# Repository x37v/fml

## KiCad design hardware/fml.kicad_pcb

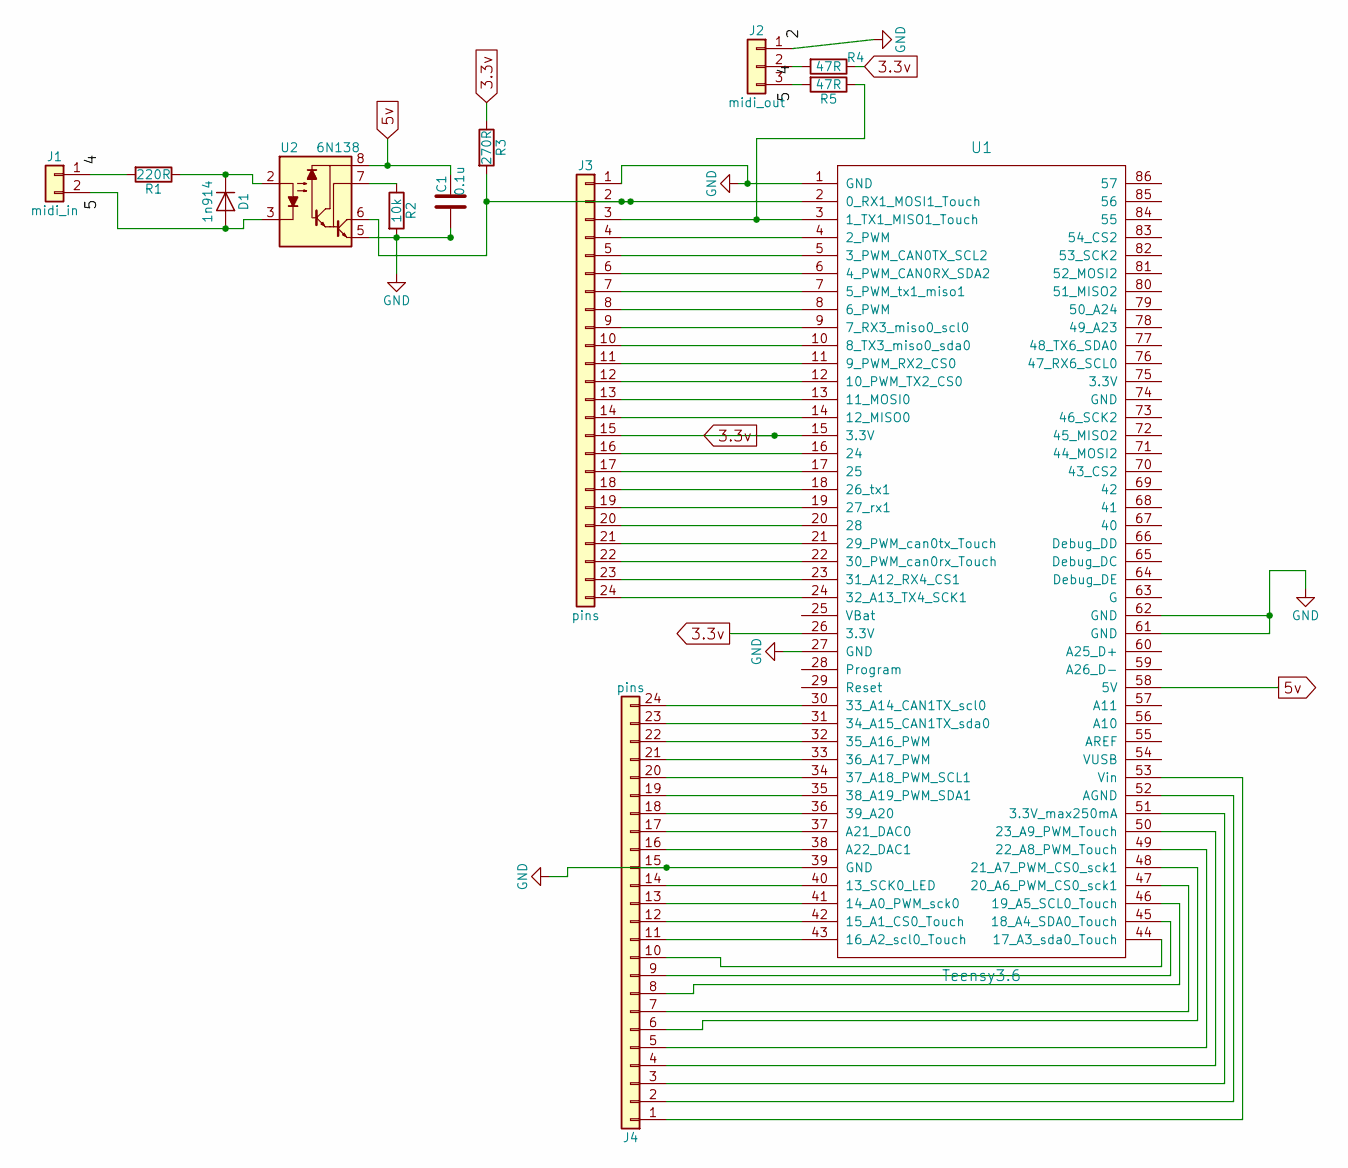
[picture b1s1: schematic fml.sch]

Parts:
C1: 0.1u; C_Disc_D5.0mm_W2.5mm_P2.50mm
D1: 1n914; D_A-405_P7.62mm_Horizontal
J1: midi_in; Pin_Header_Straight_1x02_Pitch2.54mm
J2: midi_out; Pin_Header_Straight_1x03_Pitch2.54mm
J3, J4: pins; Pin_Header_Straight_1x24_Pitch2.54mm
R1: 220R; Resistor_Horizontal_RM10mm-xnorman
R2: 10k; Resistor_Horizontal_RM10mm-xnorman
R3: 270R; Resistor_Horizontal_RM10mm-xnorman
R4, R5: 47R; Resistor_Horizontal_RM10mm-xnorman
U1: Teensy3.6; Teensy35_36
U2: 6N138; DIP-8_W7.62mm

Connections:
3.3v: J3.15, R3.1, R4.1, U1.15 (3.3V), U1.26 (3.3V)
5v: C1.2, U1.58 (5V), U2.8
GND: C1.1, J2.1, J3.1, J4.15, R2.2, U1.1 (GND), U1.27 (GND), U1.39 (GND), U1.61 (GND), U1.62 (GND), U2.5
unnamed: D1.1 (K), R1.1, U2.2
unnamed: D1.2 (A), J1.2, U2.3
unnamed: J1.1, R1.2
unnamed: J2.2, R4.2
unnamed: J2.3, R5.2
unnamed: J3.2, R3.2, U1.2 (0_RX1_MOSI1_Touch), U2.6
unnamed: J3.3, R5.1, U1.3 (1_TX1_MISO1_Touch)
unnamed: J3.4, U1.4 (2_PWM)
unnamed: J3.5, U1.5 (3_PWM_CAN0TX_SCL2)
unnamed: J3.6, U1.6 (4_PWM_CAN0RX_SDA2)
unnamed: J3.7, U1.7 (5_PWM_tx1_miso1)
unnamed: J3.8, U1.8 (6_PWM)
unnamed: J3.9, U1.9 (7_RX3_miso0_scl0)
unnamed: J3.10, U1.10 (8_TX3_miso0_sda0)
unnamed: J3.11, U1.11 (9_PWM_RX2_CS0)
unnamed: J3.12, U1.12 (10_PWM_TX2_CS0)
unnamed: J3.13, U1.13 (11_MOSI0)
unnamed: J3.14, U1.14 (12_MISO0)
unnamed: J3.16, U1.16 (24)
unnamed: J3.17, U1.17 (25)
unnamed: J3.18, U1.18 (26_tx1)
unnamed: J3.19, U1.19 (27_rx1)
unnamed: J3.20, U1.20 (28)
unnamed: J3.21, U1.21 (29_PWM_can0tx_Touch)
unnamed: J3.22, U1.22 (30_PWM_can0rx_Touch)
unnamed: J3.23, U1.23 (31_A12_RX4_CS1)
unnamed: J3.24, U1.24 (32_A13_TX4_SCK1)
unnamed: J4.1, U1.53 (Vin)
unnamed: J4.2, U1.52 (AGND)
unnamed: J4.3, U1.51 (3.3V_max250mA)
unnamed: J4.4, U1.50 (23_A9_PWM_Touch)
unnamed: J4.5, U1.49 (22_A8_PWM_Touch)
unnamed: J4.6, U1.48 (21_A7_PWM_CS0_sck1)
unnamed: J4.7, U1.47 (20_A6_PWM_CS0_sck1)
unnamed: J4.8, U1.46 (19_A5_SCL0_Touch)
unnamed: J4.9, U1.45 (18_A4_SDA0_Touch)
unnamed: J4.10, U1.44 (17_A3_sda0_Touch)
unnamed: J4.11, U1.43 (16_A2_scl0_Touch)
unnamed: J4.12, U1.42 (15_A1_CS0_Touch)
unnamed: J4.13, U1.41 (14_A0_PWM_sck0)
unnamed: J4.14, U1.40 (13_SCK0_LED)
unnamed: J4.16, U1.38 (A22_DAC1)
unnamed: J4.17, U1.37 (A21_DAC0)
unnamed: J4.18, U1.36 (39_A20)
unnamed: J4.19, U1.35 (38_A19_PWM_SDA1)
unnamed: J4.20, U1.34 (37_A18_PWM_SCL1)
unnamed: J4.21, U1.33 (36_A17_PWM)
unnamed: J4.22, U1.32 (35_A16_PWM)
unnamed: J4.23, U1.31 (34_A15_CAN1TX_sda0)
unnamed: J4.24, U1.30 (33_A14_CAN1TX_scl0)
unnamed: R2.1, U2.7

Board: 2 copper layers, 13 parts (0 on the bottom side), 54 nets, no tracks yet.

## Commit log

2015-06-20 initial setup
2015-06-20 initial setup that does nothing yet
2015-06-20 making some sound, very basic
2015-06-20 envelopes and basic synth container
2015-06-20 calculating and using dependencies in makefile
2015-06-20 setting frequency
2015-06-21 very simple note input
2015-06-21 note allocation with complete callbacks.. have some stuck note problem though
2015-06-21 no longer triggering off on reclaim voice
2015-06-21 make sure that we have non zero stage settings
2015-06-21 found stuck note problem
    the same note can be triggered multiple times. do we want this?
2015-06-21 think I've dealt with, for now.. the ramp up click sound
2015-06-21 starting to hook in CC controls
2015-06-21 mapping some CCs to envelopes
2015-06-21 toned back the feedback
2015-07-11 AD and AR envelope
2015-08-26 added description text to git project
2015-08-26 added notes for clarification
2015-09-03 updates from greg/andre meet
2015-09-03 both envelope types have callback settings now, fixed up name
2015-09-03 switched envelope types, remapping velocity
2015-09-03 passing along velocity and working with new envelope types
2015-09-03 trying to deal with immediate envelopes but they don't seem to be working quite right yet
2015-09-03 moved scaling into synth..
    depth and feedback scaling
2015-09-03 made feedback scaling a little more readable
2015-09-04 a bunch of tweaks
2015-09-04 brought velocity back in
2015-10-18 added exponential ADSR, rudimentary right now
2015-10-18 mapped in control of envelope params
2015-10-18 setting release for volume not decay, min is 15ms
2015-10-23 for testing, separated cc and note channel
    cuz quneo is sending CCs with notes..
2015-10-23 make task to run and hook up midi
2015-10-23 starting on mono mode, getting some clicking..
2015-10-24 wait a second until we try to hook to jack
2015-10-24 ignore velocity when retriggering..
    gets rid of clicks, is this how we want to work??
2015-10-25 really basic slew in place
2015-10-25 always slewing a little, getting closer
2015-10-25 defaulting to very little slew
2015-10-25 mod depth interpolation
2015-10-28 slewing velocity
2015-10-28 when a note is down in mono mode, only set freq.. don't even play with env
2015-10-29 allow for zero length attack and decay
2015-10-29 don't auto connect to audio
2015-10-29 run connected to output 3
2015-10-29 changed default settings for mod envelope
2015-10-30 working on fixed modes, frequency isn't quite right yet though
2015-10-30 fixed modes seem to work
2015-11-08 CCs now change mode in the extremes of the ratio settings
2015-11-08 connect to a bunch more midi if you can
2015-11-08 swapped fixed carrier and fixed modulator
2015-11-27 global volume control hooked up
2015-11-27 printing out more info from midiproc
2015-11-27 increased volume env's sustain to 10 seconds
2015-11-28 feedback and mod offset instantaneous phase but don't accumulate
    I think this fixes both the feedback and fine tuning issues
2015-11-28 ditched initial conditions in main for synth
2015-11-28 feedback now goes to 1
2015-11-28 smoothing modulator fine tune, always updating increments before computing
2015-11-28 linearly smoothing function, using in a bunch of places
2015-11-28 lin smooth mod depth as well
2015-11-28 much better slew, slewing freq with a linear ramp
2015-11-28 ditched mono mode
2015-11-28 slew is squared.. not sure if thats ideal but thats in the prototype
2015-12-02 removed exp slew, added more ratio steps
2015-12-02 if slew increment is zero, just jump
2015-12-02 increased the max slew increment
2015-12-09 slew is getting a little more reasonable, can turn it off now
2015-12-09 using the enumeration for env state
2015-12-09 envelope state getters
2015-12-09 new voice allocation scheme..
    same note, free note, releasing note, LRU
2015-12-10 more ratios!
2015-12-10 linearly smooth offset value, updated range in fixed mode
2015-12-10 using midi for fixed mode freq is much nicer, exponential
2015-12-15 allow for negative increments with lin_smooth
2015-12-15 using midi notes internally and slewing those, based seconds per octave
2015-12-21 only set slew note when we're idle
    this way slew will start where the synth was if its not idle
2015-12-21 removed printouts in midi proc
2015-12-21 more reasonable mod env initial settings
2015-12-21 better mod env settings, clicks gone??
2015-12-21 mod depth no longer zippery
2015-12-21 increments are stored in member variable so we know which direction we're going
    no more zipper noise?
2015-12-21 moved note and slew settings to their own method
    so we can use for mono mode
2015-12-21 mono mode midi setting, kill all notes when we switch
2015-12-21 mono mode always slews at slew rate from last note
2015-12-21 mono mode is now CC 58
2015-12-22 pitch bend!
2015-12-22 have basic transpose
2015-12-22 increased global volume
2015-12-22 stereo preparation
2015-12-22 stereo detune mode first go
2015-12-22 decreased detune
2015-12-22 fixed clicking on velocity
2015-12-22 poly mode, slewing from first held note
2015-12-22 always set slew note
2015-12-22 last of the linear smooth increment sign fixes [i think]
2015-12-22 oops, ?
2015-12-22 extended the envelopes
2015-12-22 don't turn off notes on change to mono mode
2015-12-23 using the envelope state to figure out slewing
    poly mode always slews, but if notes are held it slews from the first
    held note
    mono mode only slews when a note is held, and always slews from the last
    note hit
2015-12-23 transpose is in octave increments only
2015-12-23 moved voice allocation into 'synth'
2015-12-23 midi setting for making mod envelope linear
2015-12-23 keeping track of notes down.. to be used in mono mode
2016-01-19 smoothing feedback amount
    removed zipper noise
2016-01-19 added stm32f4xx-gcc-barebones project to start from
2016-01-19 moved barebones project
2016-01-19 renamed arm project
2016-01-19 ignoring library files and build directories
2016-01-19 updated gdb init with new project name
2016-01-19 made targets for starting openocd and gdb
2016-01-19 renamed the debug target to gdb
2016-01-21 leds work now!
2016-01-21 quick and dirty, leds now reflect button state
2016-01-21 using C++ now
2016-02-29 think i now have the dac 1/2 and full interrupts working
2016-03-03 flailing, still not hitting the interrupts i want
    I'm seeing TEIF6 and DMEIF6
2016-03-03 removed extra semicolon
2016-03-29 getting the full and half transfer callbacks..
    oops, was testing the wrong bit!!
2016-03-29 making a tone in the dma transfer.. need to work on output freq etc
2016-04-05 using the auto reload register
2016-04-05 playing with sine freq
    can't tell if its just the output not being filtered or what, it ain't
    right yet
2016-04-25 have approximately 44.1khz SR with sine wave
2016-04-25 have a chirp sound going now
2016-04-25 clean up
2016-04-25 pin layout
2016-04-25 have dual mode going but can't seem to compute sine for both without underruns
2016-04-25 computing sine just fine with arm_sin_f32
2016-04-26 reorg
2016-04-26 updated makefile and ignores
2016-04-26 fixed up clean for jack
2016-04-26 move lib to top dir and added notes about how to get it
    not including it in project because i'm not sure about the license
2016-04-26 cleaning up directories
2016-04-26 got buttons back in, increased buffer size
2016-04-28 fixed conversion from float to int12, no more clicks!
2016-04-28 oops, forgot to cleanup main
2016-04-29 making build directory if needed
2016-04-29 some of the fm code is building, need to add callbacks back
2016-04-30 added arm gcc version to readme
2016-04-30 updated readme and makefile
2016-04-30 updated readme with markdown formatting
2016-04-30 more formatting
2016-04-30 even more formatting
2016-04-30 more markdown
2016-04-30 super crippled but making sound on jack
2016-04-30 doesn't sound at all like what it should but arm chip is making sound
2016-05-20 playing a drone.. simply triggering one note
    need to optimize
2016-05-20 should have been using logf and expf all along
    also.. should find arm optimized versions
2016-05-20 ditched right channel with offset tuning
2016-05-20 changed note, fixed warning
2016-05-27 ditched callbacks and added active implementation
2016-05-27 ditched printout
2016-05-27 computing longer buffers per voice at once
2016-05-27 moved volume division to vol set, zeroed jack buffer
2016-05-27 added test pd patch for control
2016-05-27 jack interface can compute sample at a time again
    need to figure out parameter update rates with block based computations
2016-07-19 needed the floating point version of the lib
2016-07-19 not quite sure about compiler settings, but should be doing hard fpu now
2016-07-19 toggling outputs to test for timing.. TEMP
2016-07-31 ditched doubles
2016-08-01 have FM output!!!
    made an [incomplete] table of midi -> freq .. need to expand that
2016-08-01 more voices if we optimize
2016-08-01 hooked other channel up again
2016-08-01 added negative midi notes for the midi -> freq conversion
2016-08-02 getting midi callbacks, not sure if we're getting good data yet
2016-08-02 stopped working, whats up?
2016-08-02 have some serial coming in!
2016-08-02 still flailing a bit
2016-08-03 setup leds, don't try to trigger notes beyond voices
2016-08-03 midi updated per mios32 setup
2016-08-03 increased voices, triggering synth from buttons!
2016-08-08 am reading 1 channel of ADC
2016-08-08 setting mod depth with adc
2016-08-08 more volume!
2016-08-08 check for zero in lin smooth
2016-08-08 init increments and multiply by block size
2016-08-08 Indicated the analog input mapping
2016-08-08 fixed sample rate in init but cannot reinit..
2016-08-08 am now mapping a bunch of inputs on the ADC to control
2017-11-12 arduino/teensy3.6 prototype, works!
2017-11-12 added some more controls
2017-11-12 serial is optional now
2017-11-13 const expr and AUDIO_SAMPLE_RATE_EXACT
2017-11-13 use sample rate defines
2017-11-13 new envelope class, easier to grok, linear for now
2017-11-14 computing lru, ditched old callbacks
2017-11-14 made pd patch smaller
2017-11-14 defined max buffer length and increased voices
    for some reason 6 won't work.. need to optimize
2017-11-14 added velocity, cleaned up
2017-11-14 cleanup
2017-11-14 don't double smooth the modulator freq offset
2017-11-14 ditched unused var
2017-11-14 created sine method without offse
2017-11-14 can send all out now from pd patch
2017-11-14 sample period instead of rate, less division
2017-11-14 6 voices seems to work now!!
2017-11-18 using arm math helper, commented out neon that didn't work
2017-11-18 ditched the extra b.s.
2017-11-18 vectorized seems slower actually
2017-11-18 reset logic.. reset on trigger causes clicks..
2017-11-18 always triggering, reset mod env on amp end
2017-11-18 constructor arg for mode
2017-11-18 set modes for envelopes
2017-11-18 time to increment in defines
2017-11-18 direct increment setting for env, plus more safe guards
2017-11-18 allow 0 length release/attack for mod env
2017-11-18 fixed stuck note, optimized setting envelope
2017-11-18 ditch printout for now
2017-11-18 mod envelope mode controlled by sustain pedal
2017-11-18 can now bend [steppy though]
2017-11-18 script to create midi note interp
2017-11-18 generated note_to_freq
2017-11-18 have interpolated notes now!!
2017-11-19 kicad project beginning
2017-11-19 mtime
2017-11-19 more b.s.
2017-11-22 hooked up midi in and out
2017-11-22 pcb updates
2017-11-23 moved some pcb stuff around
